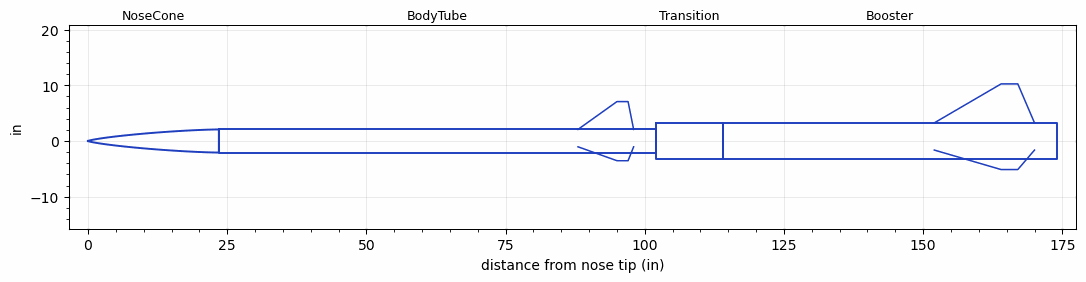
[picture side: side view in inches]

<RASAeroDocument>
 <FileVersion>2</FileVersion>
 <RocketDesign>
  <NoseCone>
   <Length>23.5</Length>
   <Diameter>4.1534</Diameter>
   <Shape>Von Karman Ogive</Shape>
   <Location>0</Location>
  </NoseCone>
  <BodyTube>
   <Length>78.5</Length>
   <Diameter>4.1534</Diameter>
   <Location>23.5</Location>
   <Fin>
    <Count>3</Count>
    <Chord>10</Chord>
    <Span>5</Span>
    <SweepDistance>7</SweepDistance>
    <TipChord>2</TipChord>
    <Thickness>0.1875</Thickness>
    <Location>14</Location>
    <AirfoilSection>Hexagonal</AirfoilSection>
    <FX1>0.86</FX1>
    <FX3>0.51</FX3>
   </Fin>
  </BodyTube>
  <Transition>
   <Length>12</Length>
   <Diameter>6.51</Diameter>
   <Location>102</Location>
   <RearDiameter>6.51</RearDiameter>
  </Transition>
  <Booster>
   <Length>60</Length>
   <Diameter>6.51</Diameter>
   <InsideDiameter>6.51</InsideDiameter>
   <Location>114</Location>
   <ShoulderLength>0</ShoulderLength>
   <Fin>
    <Count>3</Count>
    <Chord>18</Chord>
    <Span>7</Span>
    <SweepDistance>12</SweepDistance>
    <TipChord>3</TipChord>
    <Thickness>0.1875</Thickness>
    <Location>22</Location>
    <AirfoilSection>Hexagonal</AirfoilSection>
    <FX1>0.992</FX1>
    <FX3>0.544</FX3>
   </Fin>
  </Booster>
  <Surface>Rough Camouflage Paint</Surface>
  <ModifiedBarrowman>False</ModifiedBarrowman>
  <Turbulence>True</Turbulence>
  <UseBooster1>False</UseBooster1>
  <UseBooster2>False</UseBooster2>
 </RocketDesign>
 <LaunchSite>
  <Altitude>0</Altitude>
  <Pressure>0</Pressure>
  <RodAngle>0</RodAngle>
  <RodLength>4</RodLength>
  <Temperature>74</Temperature>
  <WindSpeed>0</WindSpeed>
 </LaunchSite>
 <Recovery>
  <Altitude1>1000</Altitude1>
  <Altitude2>1000</Altitude2>
  <DeviceType1>None</DeviceType1>
  <DeviceType2>None</DeviceType2>
  <Event1>False</Event1>
  <Event2>False</Event2>
  <Size1>1</Size1>
  <Size2>1</Size2>
  <EventType1>None</EventType1>
  <EventType2>None</EventType2>
  <CD1>1.33</CD1>
  <CD2>1.33</CD2>
 </Recovery>
 <SimulationList>
  <Simulation>
   <SustainerEngine>BERMA-25000-02  (Karman_AIAA-capstone)</SustainerEngine>
   <SustainerLaunchWt>44.44</SustainerLaunchWt>
   <SustainerNozzleDiameter>4</SustainerNozzleDiameter>
   <SustainerCG>71</SustainerCG>
   <SustainerIgnitionDelay>24</SustainerIgnitionDelay>
   <Booster1Engine>O8000  (CTI)</Booster1Engine>
   <Booster1LaunchWt>135.83</Booster1LaunchWt>
   <Booster1SeparationDelay>0</Booster1SeparationDelay>
   <Booster1IgnitionDelay>0</Booster1IgnitionDelay>
   <Booster1CG>116</Booster1CG>
   <Booster1NozzleDiameter>6</Booster1NozzleDiameter>
   <IncludeBooster1>True</IncludeBooster1>
   <Booster2Delay>0</Booster2Delay>
   <IncludeBooster2>False</IncludeBooster2>
   <TimetoApogee>204.8396</TimetoApogee>
   <MaxAltitude>498560</MaxAltitude>
   <MaxVelocity>6361.703</MaxVelocity>
   <OptimumWt>28.83266</OptimumWt>
   <OptimumMaxAlt>28.83266</OptimumMaxAlt>
  </Simulation>
  <Simulation>
   <SustainerEngine>BERMA-25000-02  (Karman_AIAA-capstone)</SustainerEngine>
   <SustainerLaunchWt>48</SustainerLaunchWt>
   <SustainerNozzleDiameter>4</SustainerNozzleDiameter>
   <SustainerCG>70</SustainerCG>
   <SustainerIgnitionDelay>24</SustainerIgnitionDelay>
   <Booster1Engine>O8000  (CTI)</Booster1Engine>
   <Booster1LaunchWt>132</Booster1LaunchWt>
   <Booster1SeparationDelay>0</Booster1SeparationDelay>
   <Booster1IgnitionDelay>0</Booster1IgnitionDelay>
   <Booster1CG>126</Booster1CG>
   <Booster1NozzleDiameter>6</Booster1NozzleDiameter>
   <IncludeBooster1>True</IncludeBooster1>
   <Booster2Delay>0</Booster2Delay>
   <IncludeBooster2>False</IncludeBooster2>
   <TimetoApogee>191.9666</TimetoApogee>
   <MaxAltitude>435236.6</MaxAltitude>
   <MaxVelocity>5807.303</MaxVelocity>
   <OptimumWt>31.35938</OptimumWt>
   <OptimumMaxAlt>31.35938</OptimumMaxAlt>
  </Simulation>
 </SimulationList>
</RASAeroDocument>
